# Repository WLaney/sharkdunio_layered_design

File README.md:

# sharkduino_layered_desgine

This repository contains the Eagle designs and design information for the Sharkduino PCBs. The name sharkduino_layered_desgin is a legacy name referring to the design type used by Sharkduino V1. This repository does however contains all versions of Shakrduino, not just V1. Please see [Sharkduino Versions](#sharkduino-versions) for more information. For the spefic chips and ports on each version please see [Hardware Quick Reference](https://github.com/WLaney/sharkdunio_layered_design/blob/master/hardware_quick_reference.md)

# Sharkduino Versions

This is an explanation of the different sharkduino versions and the directories in this repository that contain them

## Sharkduino V1

Sharkduino V1 uses a layer designs and consists of [layer1](layer1/), [layer2](layer2/), and [layer3](layer3/). The versions of Sharkduino V1 that were assembled corresponded to the release v2 named "Layered boards". Changes have been made to the boards since then in order to improve them, these changes constitute Sharkduino V1.1. No V1.1 boards were ever ordered or assembled. Instead of ordering V1.1 boards a design overhaul took place and we moved to Sharkduino V2. 

## Sharkduino V2

Sharkduino V2 constitutes a design overhaul from V1 with a new board shape and new set of sensors. These designs can be found in the [trapezoid](trapezoid/) directory. The version of Sharkduino V2 that has been assembled corresponds to release [v5](https://github.com/WLaney/sharkdunio_layered_design/releases/tag/v5) "Sharkduion V2". Since the enviromental sensors need to be sepreate from the movement sensors Shakrduino V2 still uses [layer3](layer3/) form the Sharkduino V1 as no changes to that board were nessary.

## Sharkduino V2.1

Sharkduino V2.1 is an identical PCB to V2, but it uses the MMA8451 accelerometer. This is opposed to the MMA8452 used in the V2. This change was made so that the accelerometer would have a FIFO bufer like the gyroscope. The new accelerometer is an expermental change, so the files are on the [MMA8451 branch](https://github.com/WLaney/sharkdunio_layered_design/tree/mma8451). The first functinoal build of this corosponds to release [v7](https://github.com/WLaney/sharkdunio_layered_design/releases/tag/v7). The change on this branch have since been merged into master.

## Sharkduino V2.2

Sharkduino V2.2 is a slight varation on the Sharkduino V2.x desgine. Due to the [issue with the cargining circuity](https://github.com/WLaney/sharkdunio_layered_design/issues/1) the microUSB and lipo charger were removed from the board. This was done in order to have a set of fully functional board ready for summer 2017. 

The LiPo plug was moved to the top of the board in order to streamline the desgine. Additionaly interupt pin2 on the FXAS21002 gyroscope was connected Arduino pin 2. 

Since in the long term we plan to fix the LiPo charging issue, instead of removing the LiPo chargin all together as we have done here, the files for Sharkduino V2.2 are on the [no_chargin branch](https://github.com/WLaney/sharkdunio_layered_design/tree/no_charging) and will never be merged into master. The desgines of the Sharkduino V2.2 that have been order corosponed to release [v8](https://github.com/WLaney/sharkdunio_layered_design/releases/tag/v8).

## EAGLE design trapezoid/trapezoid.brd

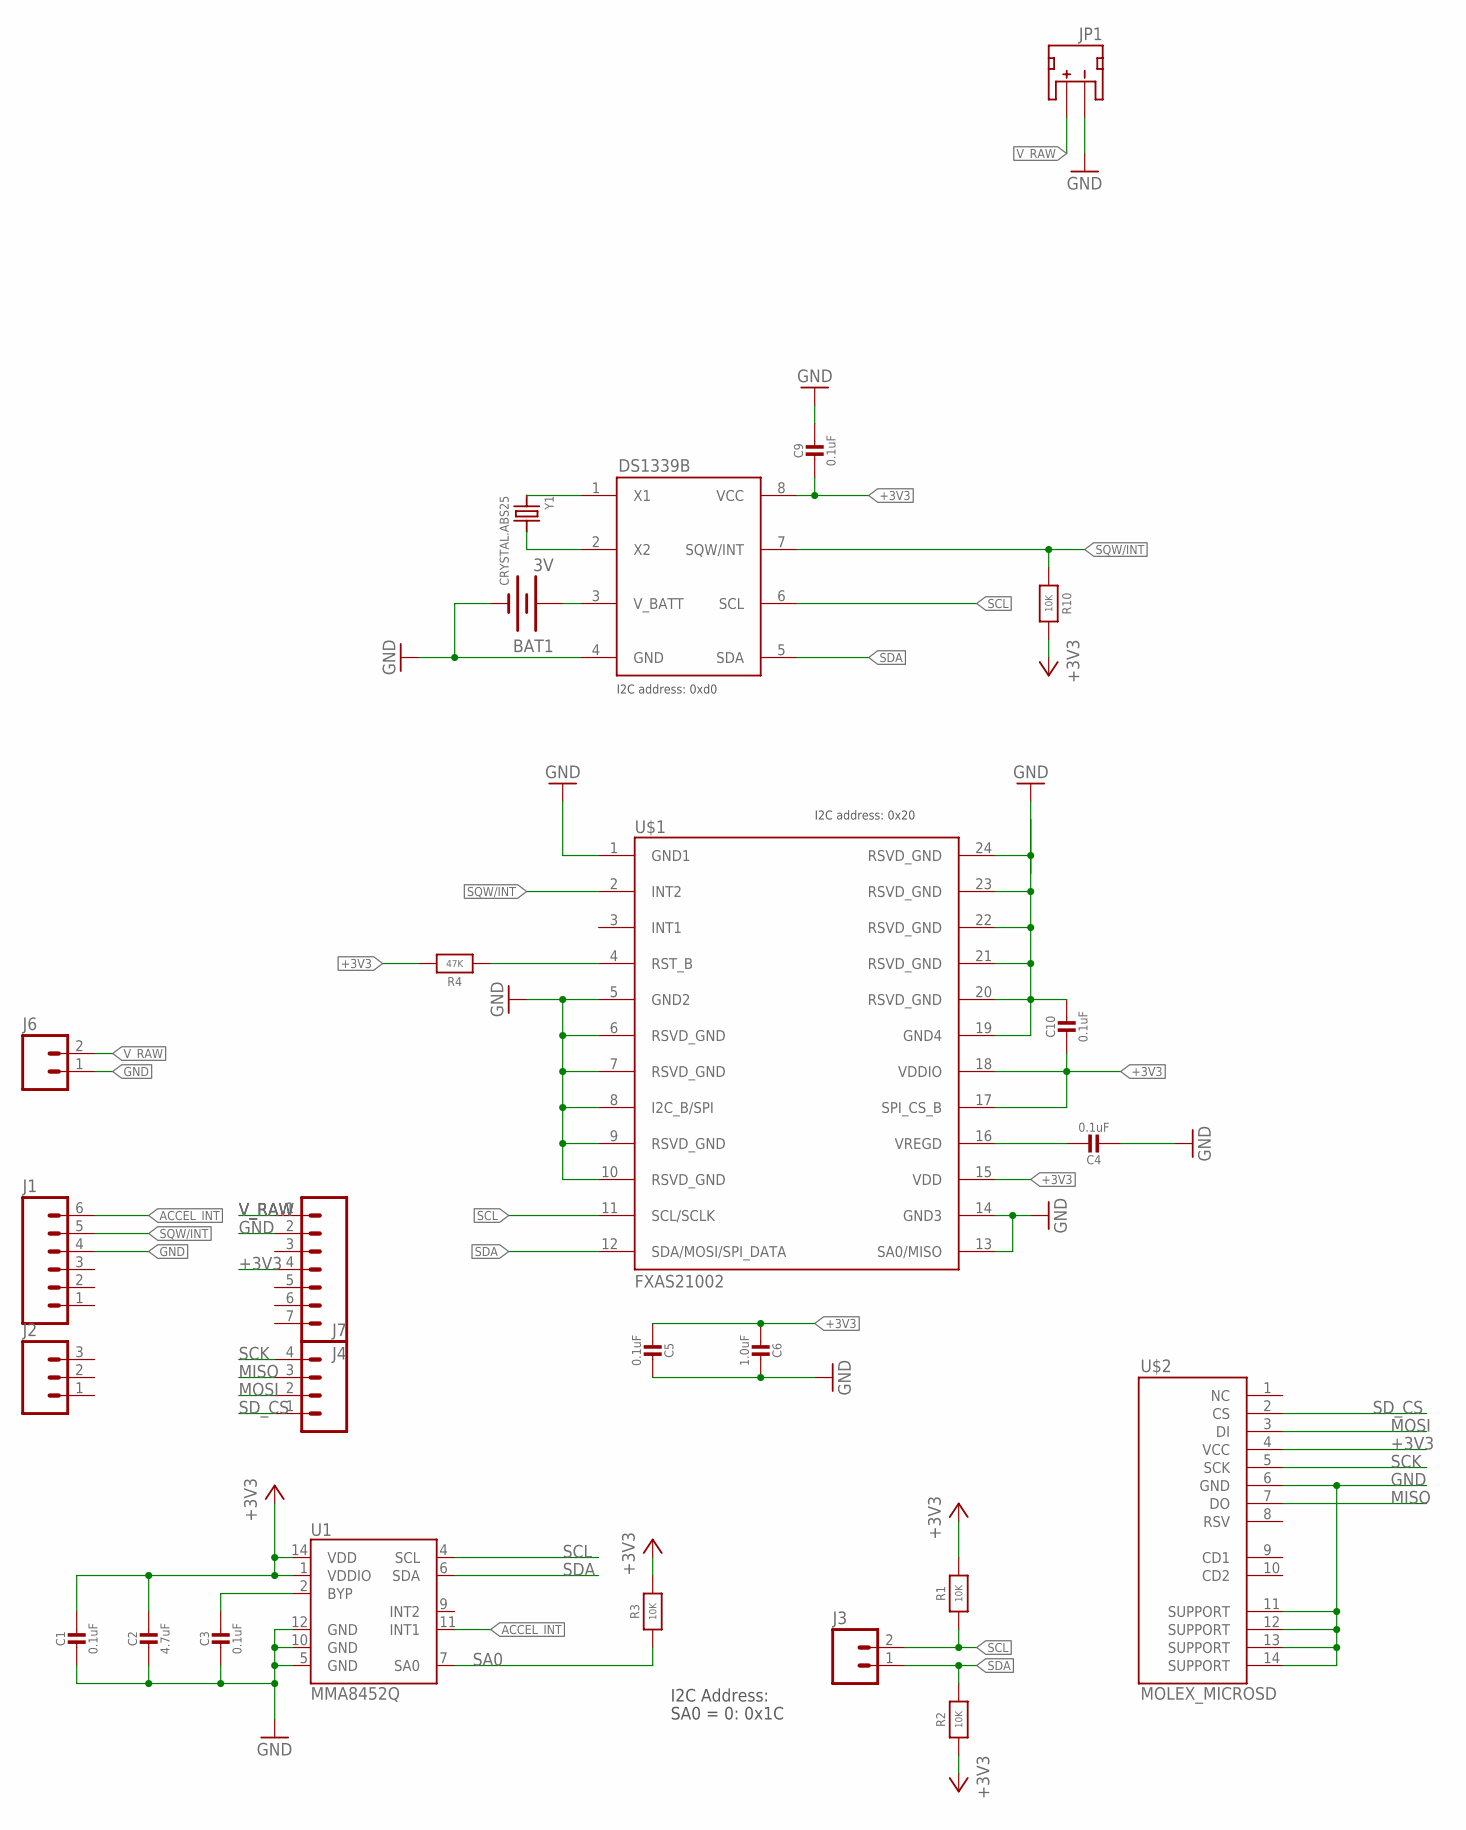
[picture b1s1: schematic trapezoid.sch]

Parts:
BAT1: 3V; BATTCON_12MM_CURVED
C1, C3, C4, C5, C9, C10: 0.1uF; 0805-NO
C2: 4.7uF; 0805-NO
C6: 1.0uF; 0805-NO
J1: M06SILK_FEMALE_PTH; 1X06
J2: M03PTH; 1X03
J3, J6: M02LOCK; 1X02_LOCK
J4: M07; 1X07
J7: M04PTH; 1X04
JP1: JST; JST-2-SMD@1
R1, R2, R10: 10K; 0805-NO
R3: 10K; _0805MP
R4: 47K; 0805-NO
U1: MMA8452Q; QFN-16_0.5MM
U$1: FXAS21002; 24QFN
U$2: MOLEX_MICROSD
U$3: DS1339BDS1339B; 8U-SOP
Y1: CRYSTAL.ABS25; ABS25

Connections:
+3V3: C1.1, C2.1, C5.2, C6.2, C9.2, C10.2, J4.4, R1.2, R2.1, R3.2, R4.2, R10.2, U1.1 (VDDIO), U1.14 (VDD), U$1.15 (VDD), U$1.17 (SPI_CS_B), U$1.18 (VDDIO), U$2.4 (VCC), U$3.8 (VCC)
ACCEL_INT: J1.6, U1.11 (INT1)
BYP: C3.1, U1.2 (BYP)
GND: BAT1.GND (-), C1.2, C2.2, C3.2, C4.2, C5.1, C6.1, C9.1, C10.1, J1.4, J4.2, J6.1, JP1.1 (-), U1.5 (GND), U1.10 (GND), U1.12 (GND), U$1.1 (GND1), U$1.5 (GND2), U$1.6 (RSVD_GND), U$1.7 (RSVD_GND), U$1.8 (I2C_B/SPI), U$1.9 (RSVD_GND), U$1.10 (RSVD_GND), U$1.13 (SA0/MISO), U$1.14 (GND3), U$1.19 (GND4), U$1.20 (RSVD_GND), U$1.21 (RSVD_GND), U$1.22 (RSVD_GND), U$1.23 (RSVD_GND), U$1.24 (RSVD_GND), U$2.6 (GND), U$2.11 (SUPPORT), U$2.12 (SUPPORT), U$2.13 (SUPPORT), U$2.14 (SUPPORT), U$3.4 (GND)
MISO: J7.3, U$2.7 (DO)
MOSI: J7.2, U$2.3 (DI)
unnamed: U$3.2 (X2), Y1.4 (2)
unnamed: C4.1, U$1.16 (VREGD)
unnamed: BAT1.PWR@1 (+), U$3.3 (V_BATT)
unnamed: U$3.1 (X1), Y1.1
unnamed: R4.1, U$1.4 (RST_B)
SA0: R3.1, U1.7 (SA0)
SCK: J7.4, U$2.5 (SCK)
SCL: J3.2, R1.1, U1.4 (SCL), U$1.11 (SCL/SCLK), U$3.6 (SCL)
SDA: J3.1, R2.2, U1.6 (SDA), U$1.12 (SDA/MOSI/SPI_DATA), U$3.5 (SDA)
SD_CS: J7.1, U$2.2 (CS)
SQW/INT: J1.5, R10.1, U$1.2 (INT2), U$3.7 (SQW/INT)
V_RAW: J4.1, J6.2, JP1.2 (+)

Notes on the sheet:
I2C Address:
SA0 = 0: 0x1C
I2C address: 0xd0
I2C address: 0x20

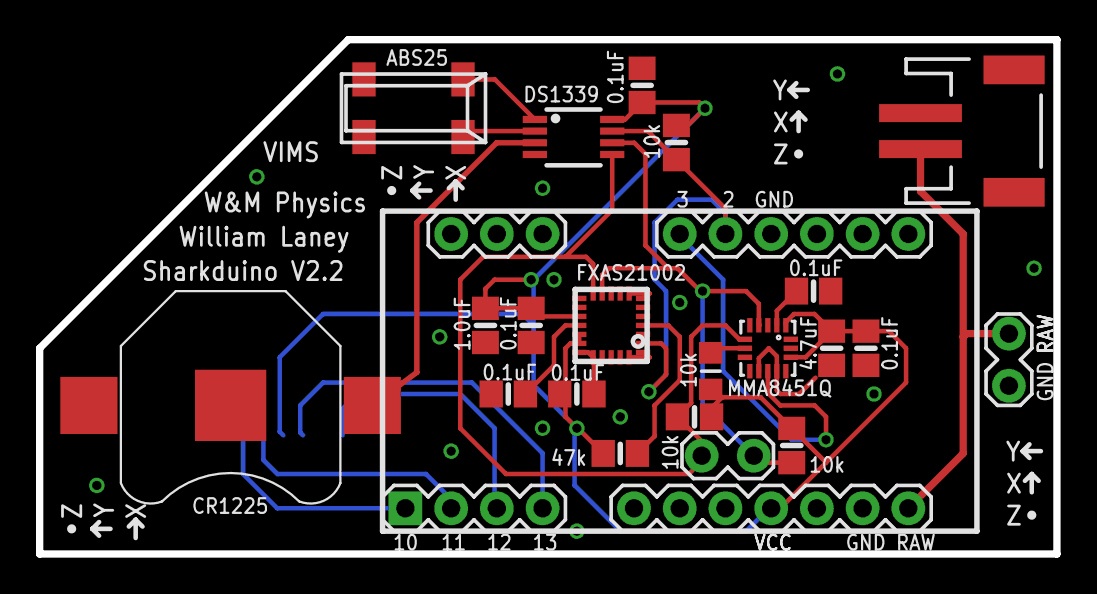
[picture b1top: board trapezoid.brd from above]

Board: 2 copper layers, 56.5 x 28.6 mm, 26 parts (1 on the bottom side), 18 nets.

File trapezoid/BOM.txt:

component/value, size, quanity, digikey part number
--------------------------------------------------------
Arduino Pro Mini 3.3V/8MHz, NA, 1, 1568-1054-ND
MMA8451QT, 16-VFQFN, 1, MMA8451QT-ND
FXAS21002 IC, 24-TFQFN, 1, FXAS21002CQR1CT-ND
DS1339B IC, 8-TSSOP/8-MSOP, 1, DS1339BU+-ND
Abracon LLC ABS25-32.768KHZ-T, 4-SOJ, 1, 535-9166-1-ND
Molex 8+2 microSD slot, NA, 1, WM6357CT-ND
0.1uF capacitor, 0805, 6, 478-3755-1-ND
1.0uF capacitor, 0805, 1, 311-1365-1-ND
4.7uF capacitor, 0805, 1, 490-3335-1-ND
10K resistor, 0805, 4, 311-10.0KCRCT-ND
47k resistor, 0805, 1, 311-47KARCT-ND
Curved Battery Holder, 12mm, 1, 36-3000CT-ND
JST Male, 2mm, 1, 455-1749-1-ND
Male Header Pins, 0.10", 1, S1011EC-40-ND

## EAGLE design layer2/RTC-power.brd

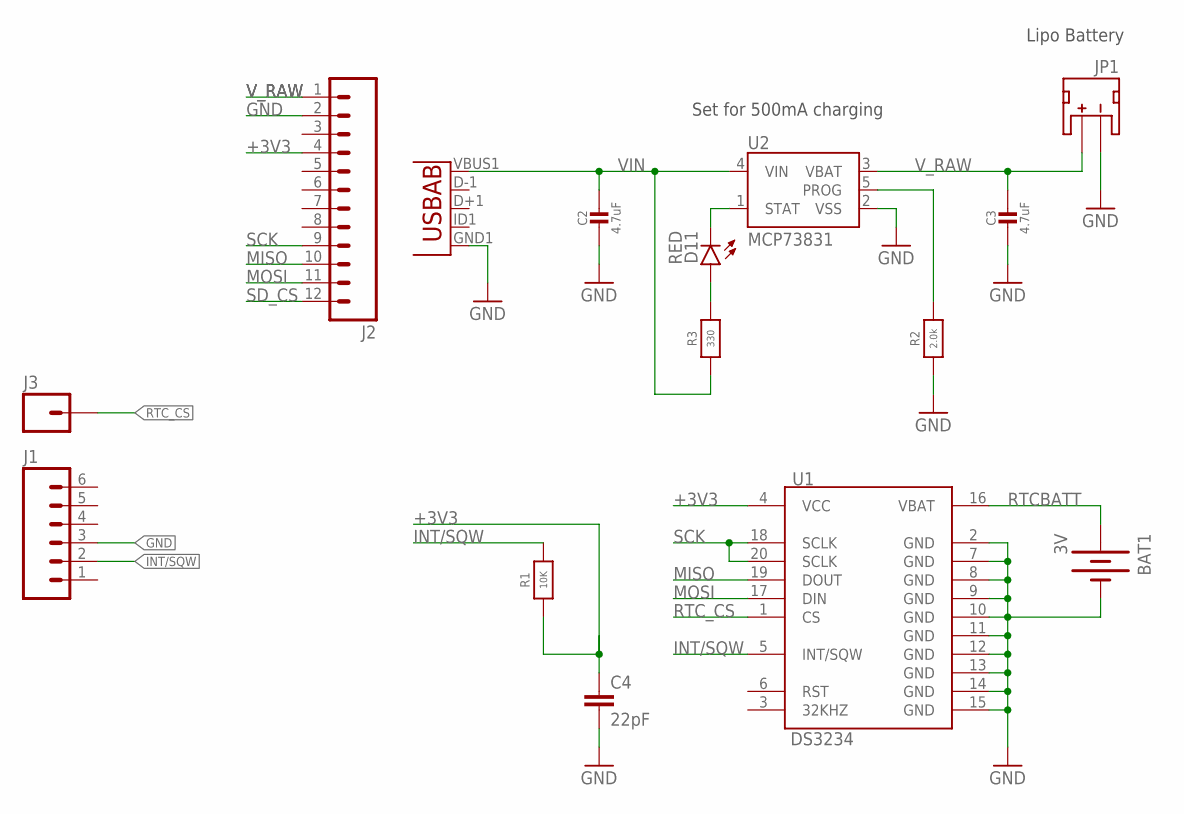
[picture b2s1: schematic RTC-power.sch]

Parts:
BAT1: 3V; BATTCON_12MM_CURVED
C2, C3: 4.7uF; 0805-NO
C4: 22pF; 0402-CAP
D11: RED; LED-0603
J1: M06SILK_FEMALE_PTH; 1X06
J2: M12PTH; 1X12
J3: M01PTH; 1X01
JP1: JST; JST-2-SMD@1
JP9: Micro USB; USB-AB-MICRO-SMD_V03
R1: 10K; _0805MP
R2: 2.0k; _0805MP
R3: 330; _0805MP
U1: DS3234
U2: MCP73831; SOT23-5

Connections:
+3V3: C4.1, J2.4, R1.1, U1.4 (VCC)
GND: BAT1.GND (-), C2.2, C3.2, C4.2, J2.2, JP1.1 (-), JP9.GND1 (GND), R2.1, U1.2 (GND), U1.7 (GND), U1.8 (GND), U1.9 (GND), U1.10 (GND), U1.11 (GND), U1.12 (GND), U1.13 (GND), U1.14 (GND), U1.15 (GND), U2.2 (VSS)
INT/SQW: R1.2, U1.5 (INT/SQW)
MISO: J2.10, U1.19 (DOUT)
MOSI: J2.11, U1.17 (DIN)
unnamed: D11.A, R3.2
PROG: R2.2, U2.5 (PROG)
RTCBATT: BAT1.PWR@1 (+), U1.16 (VBAT)
RTC_CS: J3.1, U1.1 (CS)
SCK: J2.9, U1.18 (SCLK), U1.20 (SCLK)
SD_CS: J2.12
STAT: D11.C, U2.1 (STAT)
VIN: C2.1, JP9.VBUS1 (VBUS), R3.1, U2.4 (VIN)
V_RAW: C3.1, J2.1, JP1.2 (+), U2.3 (VBAT)

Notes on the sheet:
Set for 500mA charging
Lipo Battery

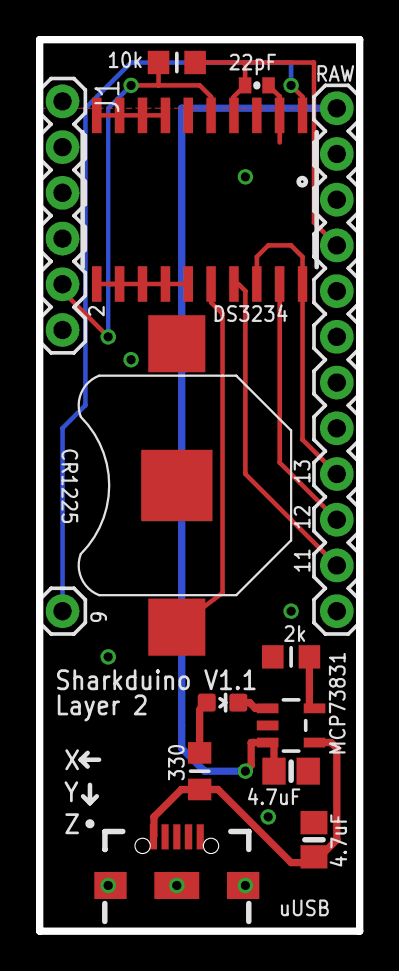
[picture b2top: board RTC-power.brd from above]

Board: 2 copper layers, 17.8 x 49.5 mm, 15 parts (1 on the bottom side), 13 nets.

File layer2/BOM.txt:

component/value, size, quanity, digikey part number
--------------------------------------------------------
4.7uF capacitor, 0805, 2, 490-3335-1-ND
22pF capacitor, 0402, 1, 399-7774-1-ND
Red LED, 0603, 1, 160-1447-1-ND
10K resistor, 0805, 1, 311-10.0KCRCT-ND
2k resistor, 0805, 1, 311-2.00KCRCT-ND
330 resistor, 0805, 1, 311-330CRCT-ND
DS3234 IC, NA, 1, 	DS3234S#T&RCT-ND
MCP73831 IC, NA, 1, MCP73831T-2ATI/OTCT-ND
Curved Battery Holder, 12mm, 1, 36-3000CT-ND
JST Male, 2mm, 1, 455-1704-ND *NOT THE RIGHT PART*
USB micro SMD, NA, 1, 609-4053-1-ND
Header Pins, NA, 1, S1131EC-40-ND

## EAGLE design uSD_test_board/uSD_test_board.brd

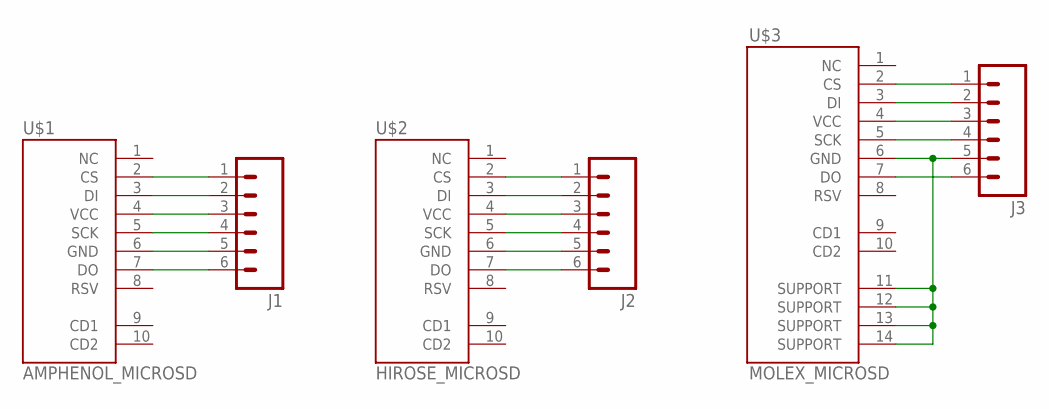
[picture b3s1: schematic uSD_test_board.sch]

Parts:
J1, J2, J3: M06SILK_FEMALE_PTH; 1X06
U$1: AMPHENOL_MICROSD
U$2: HIROSE_MICROSD; AMPHENOL_MICROSD
U$3: MOLEX_MICROSD

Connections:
CS1: J1.1, U$1.2 (CS)
CS2: J2.1, U$2.2 (CS)
CS3: J3.1, U$3.2 (CS)
DI1: J1.2, U$1.3 (DI)
DI2: J2.2, U$2.3 (DI)
DI3: J3.2, U$3.3 (DI)
DO1: J1.6, U$1.7 (DO)
DO2: J2.6, U$2.7 (DO)
DO3: J3.6, U$3.7 (DO)
GND: J1.5, J2.5, J3.5, U$1.6 (GND), U$2.6 (GND), U$3.6 (GND), U$3.11 (SUPPORT), U$3.12 (SUPPORT), U$3.13 (SUPPORT), U$3.14 (SUPPORT)
SCK1: J1.4, U$1.5 (SCK)
SCK2: J2.4, U$2.5 (SCK)
SCK3: J3.4, U$3.5 (SCK)
VCC1: J1.3, U$1.4 (VCC)
VCC2: J2.3, U$2.4 (VCC)
VCC3: J3.3, U$3.4 (VCC)

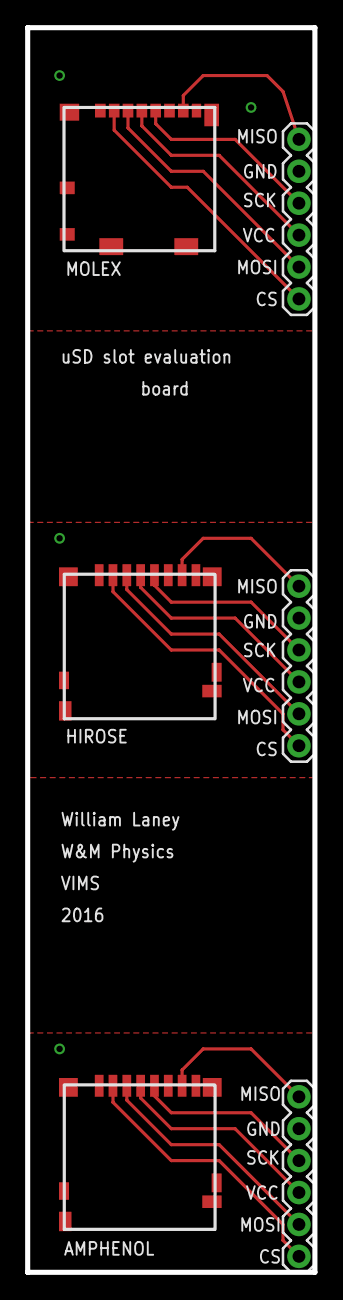
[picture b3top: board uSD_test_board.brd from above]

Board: 2 copper layers, 22.9 x 99.1 mm, 6 parts (0 on the bottom side), 16 nets.

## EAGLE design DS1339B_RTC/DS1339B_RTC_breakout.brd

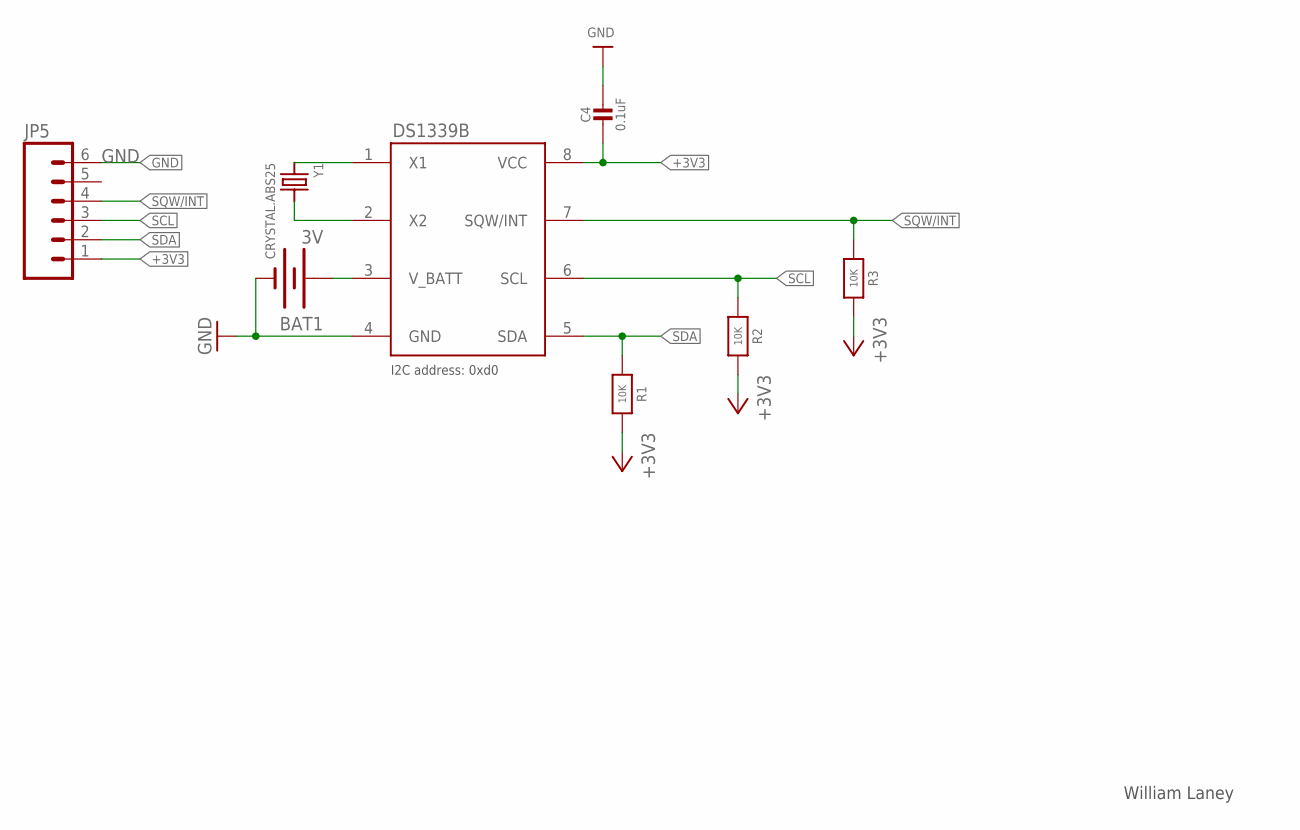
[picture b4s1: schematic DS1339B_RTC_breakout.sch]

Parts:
BAT1: 3V; BATTCON_12MM_CURVED
C4: 0.1uF; 0805-NO
JP5: M06SIP; 1X06
R1, R2, R3: 10K; 0805-NO
U$1: DS1339BDS1339B; 8U-SOP
Y1: CRYSTAL.ABS25; ABS25

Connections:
+3V3: C4.2, JP5.1, R1.2, R2.2, R3.2, U$1.8 (VCC)
GND: BAT1.GND (-), C4.1, JP5.6, U$1.4 (GND)
unnamed: U$1.1 (X1), Y1.1
unnamed: U$1.2 (X2), Y1.4 (2)
unnamed: BAT1.PWR@1 (+), U$1.3 (V_BATT)
SCL: JP5.3, R2.1, U$1.6 (SCL)
SDA: JP5.2, R1.1, U$1.5 (SDA)
SQW/INT: JP5.4, R3.1, U$1.7 (SQW/INT)

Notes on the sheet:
I2C address: 0xd0
William Laney

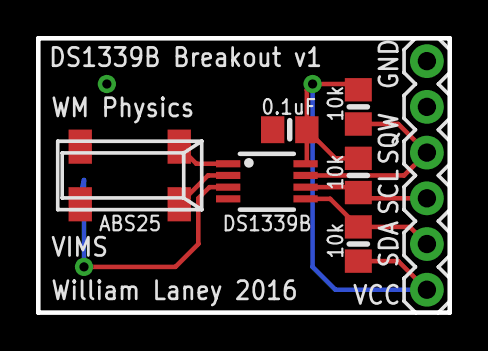
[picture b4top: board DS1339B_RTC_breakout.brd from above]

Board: 2 copper layers, 22.9 x 15.2 mm, 8 parts (1 on the bottom side), 8 nets.

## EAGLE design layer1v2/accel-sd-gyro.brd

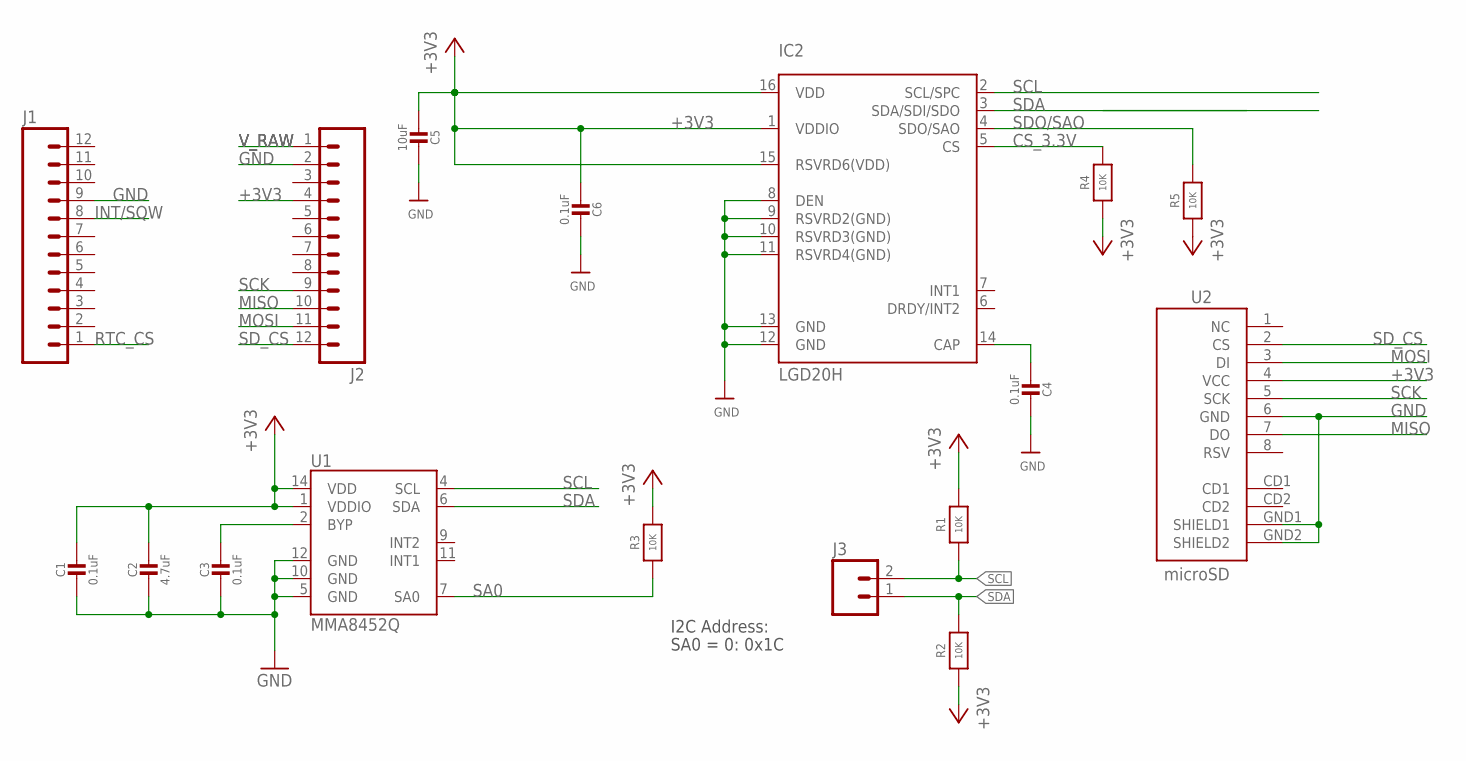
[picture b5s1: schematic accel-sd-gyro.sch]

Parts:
C1, C3, C4, C6: 0.1uF; 0805-NO
C2: 4.7uF; 0805-NO
C5: 10uF; 0805-NO
IC2: LGD20H; L3GD20H_LGA16L
J1, J2: M12PTH; 1X12
J3: M02LOCK; 1X02_LOCK
R1, R2, R4, R5: 10K; 0805-NO
R3: 10K; _0805MP
U1: MMA8452Q; QFN-16_0.5MM
U2: microSD; MICRO-SD-SOCKET-PP

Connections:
+3V3: C1.1, C2.1, C5.2, C6.2, IC2.1 (VDDIO), IC2.15 (RSVRD6(VDD)), IC2.16 (VDD), J2.4, R1.2, R2.1, R3.2, R4.1, R5.1, U1.1 (VDDIO), U1.14 (VDD), U2.4 (VCC)
BYP: C3.1, U1.2 (BYP)
CS_3.3V: IC2.5 (CS), R4.2
GND: C1.2, C2.2, C3.2, C4.1, C5.1, C6.1, IC2.8 (DEN), IC2.9 (RSVRD2(GND)), IC2.10 (RSVRD3(GND)), IC2.11 (RSVRD4(GND)), IC2.12 (GND), IC2.13 (GND), J1.9, J2.2, U1.5 (GND), U1.10 (GND), U1.12 (GND), U2.6 (GND), U2.GND1 (SHIELD1), U2.GND2 (SHIELD2)
INT/SQW: J1.8
MISO: J2.10, U2.7 (DO)
MOSI: J2.11, U2.3 (DI)
unnamed: C4.2, IC2.14 (CAP)
RTC_CS: J1.1
SA0: R3.1, U1.7 (SA0)
SCK: J2.9, U2.5 (SCK)
SCL: IC2.2 (SCL/SPC), J3.2, R1.1, U1.4 (SCL)
SDA: IC2.3 (SDA/SDI/SDO), J3.1, R2.2, U1.6 (SDA)
SDO/SAO: IC2.4 (SDO/SAO), R5.2
SD_CS: J2.12, U2.2 (CS)
V_RAW: J2.1

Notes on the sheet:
I2C Address:
SA0 = 0: 0x1C

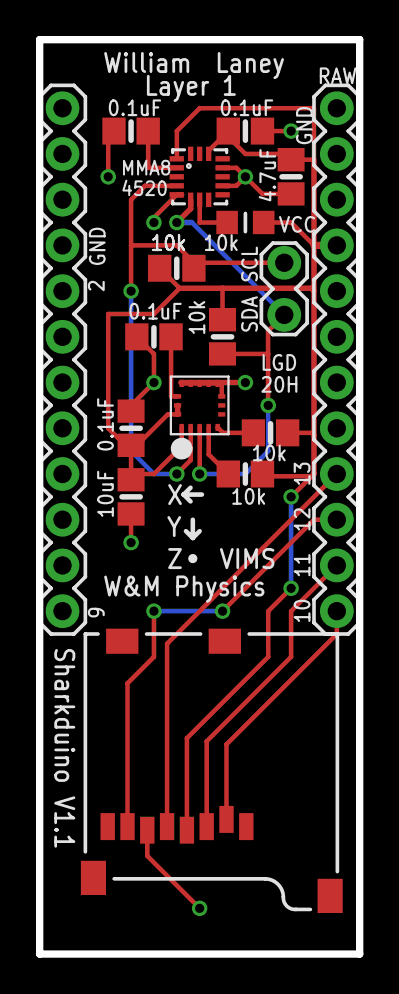
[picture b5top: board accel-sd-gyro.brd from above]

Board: 2 copper layers, 17.8 x 50.8 mm, 17 parts (0 on the bottom side), 13 nets.

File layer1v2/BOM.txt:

component/value, size, quanity, digikey part number
--------------------------------------------------------
0.1uF capacitor, 0805, 4, 478-3755-1-ND
4.7uF capacitor, 0805, 1, 490-3335-1-ND
10uF capacitor, 0805, 1, 490-4735-1-ND
10K resistor, 0805, 4, 311-10.0KCRCT-ND
MMA8452QT, NA, 1, 	MMA8452QT-ND
L3GD20HTR IC, NA, 1, 497-13931-1-ND
microSD SMD, NA, 1, Sparkfun: PRT-00127

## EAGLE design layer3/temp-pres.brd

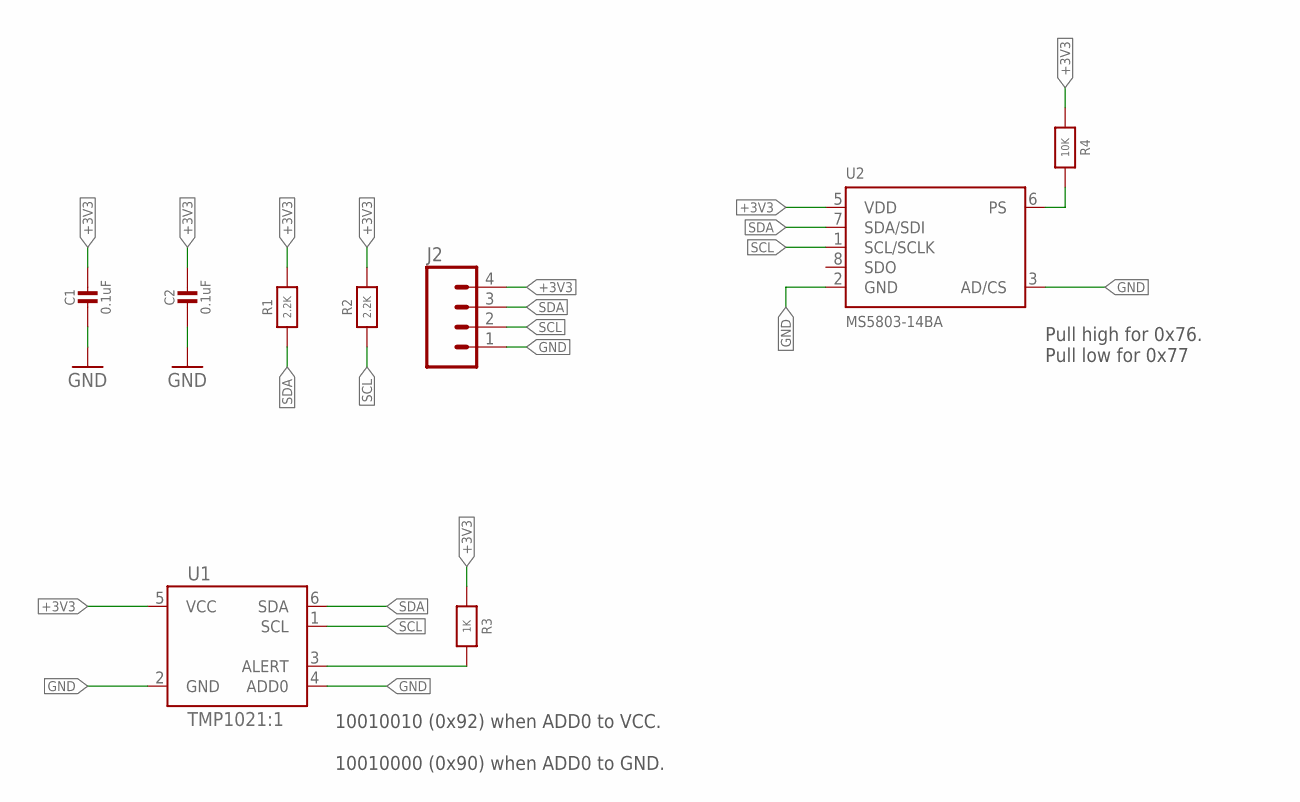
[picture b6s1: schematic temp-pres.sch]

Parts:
C1, C2: 0.1uF; 0805-NO
J2: M04NO_SILK_ALL_ROUND; 1X04_NO_SILK_ALL_ROUND
R1, R2: 2.2K; _0805MP
R3: 1K; _0805MP
R4: 10K; _0805MP
U1: TMP1021:1; SOT563-2
U2: MS5803-14BA; MS5803

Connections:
+3V3: C1.1, C2.1, J2.4, R1.2, R2.2, R3.1, R4.1, U1.5 (VCC), U2.5 (VDD)
GND: C1.2, C2.2, J2.1, U1.2 (GND), U1.4 (ADD0), U2.2 (GND), U2.3 (AD/CS)
unnamed: R3.2, U1.3 (ALERT)
PS: R4.2, U2.6 (PS)
SCL: J2.2, R2.1, U1.1 (SCL), U2.1 (SCL/SCLK)
SDA: J2.3, R1.1, U1.6 (SDA), U2.7 (SDA/SDI)

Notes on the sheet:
10010010 (0x92) when ADD0 to VCC. 10010000 (0x90) when ADD0 to GND.
Pull high for 0x76. Pull low for 0x77

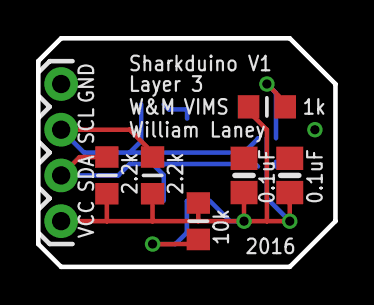
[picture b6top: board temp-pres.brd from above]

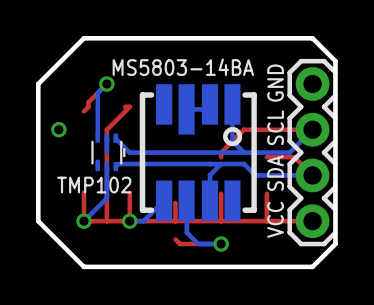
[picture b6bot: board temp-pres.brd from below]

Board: 2 copper layers, 16.5 x 12.7 mm, 9 parts (2 on the bottom side), 6 nets.

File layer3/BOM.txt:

component/value, size, quanity, digikey part number
--------------------------------------------------------
10K resistor, 0805, 1, 311-10.0KCRCT-ND
2.2K resistor, 0805, 2, 311-2.20KCRCT-ND
1k resostor, 0805, 1, 311-1.00KCRCT-ND
0.1uF capacitor, 0805, 2, 478-3755-1-ND
TMP102 IC, NA, 1, 296-26834-1-ND
MS5803-14BA IC, NA, 1, 223-1626-5-ND

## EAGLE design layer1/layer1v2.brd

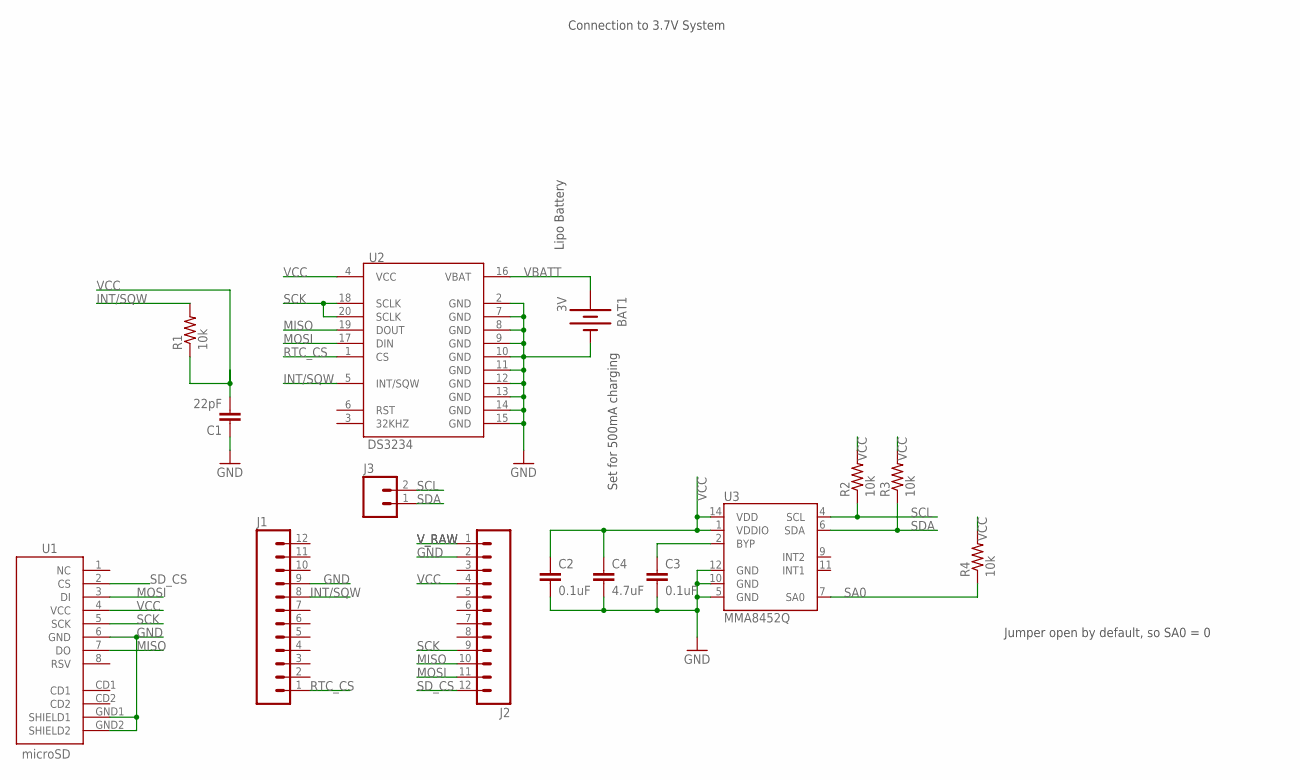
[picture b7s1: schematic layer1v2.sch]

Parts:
BAT1: 3V; BATTCON_12MM_CURVED
C1: 22pF; 0402-CAP
C2, C3: 0.1uF; 0402-CAP
C4: 4.7uF; 0402-CAP
J1, J2: M12PTH; 1X12
J3: M02LOCK; 1X02_LOCK
R1, R2, R3, R4: 10k; 0402-RES
U1: microSD; MICRO-SD-SOCKET-PP
U2: DS3234
U3: MMA8452Q; QFN-16_0.5MM

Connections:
BYP: C3.1, U3.2 (BYP)
GND: BAT1.GND (-), C1.1, C2.2, C3.2, C4.2, J1.9, J2.2, U1.6 (GND), U1.GND1 (SHIELD1), U1.GND2 (SHIELD2), U2.2 (GND), U2.7 (GND), U2.8 (GND), U2.9 (GND), U2.10 (GND), U2.11 (GND), U2.12 (GND), U2.13 (GND), U2.14 (GND), U2.15 (GND), U3.5 (GND), U3.10 (GND), U3.12 (GND)
INT/SQW: J1.8, R1.2, U2.5 (INT/SQW)
MISO: J2.10, U1.7 (DO), U2.19 (DOUT)
MOSI: J2.11, U1.3 (DI), U2.17 (DIN)
RTC_CS: J1.1, U2.1 (CS)
SA0: R4.1, U3.7 (SA0)
SCK: J2.9, U1.5 (SCK), U2.18 (SCLK), U2.20 (SCLK)
SCL: J3.2, R2.1, U3.4 (SCL)
SDA: J3.1, R3.1, U3.6 (SDA)
SD_CS: J2.12, U1.2 (CS)
VBATT: BAT1.PWR@1 (+), U2.16 (VBAT)
VCC: C1.2, C2.1, C4.1, J2.4, R1.1, R2.2, R3.2, R4.2, U1.4 (VCC), U2.4 (VCC), U3.1 (VDDIO), U3.14 (VDD)
V_RAW: J2.1

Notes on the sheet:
Set for 500mA charging
Connection to 3.7V System
Lipo Battery
Jumper open by default, so SA0 = 0

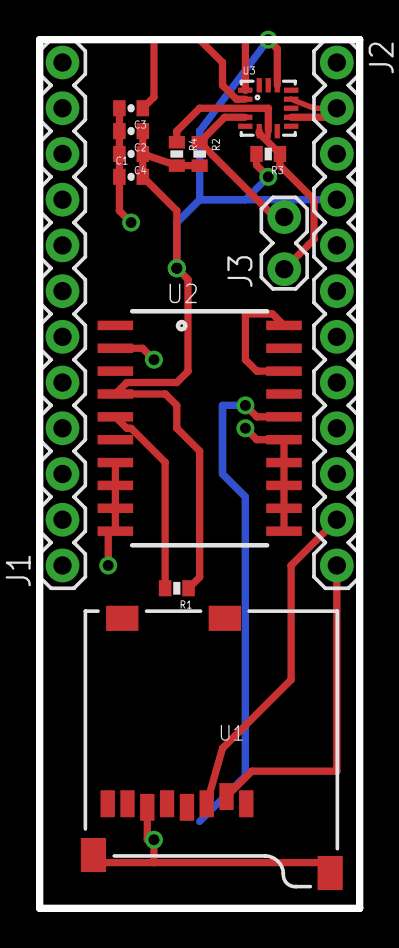
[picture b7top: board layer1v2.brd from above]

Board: 2 copper layers, 17.8 x 48.3 mm, 15 parts (1 on the bottom side), 13 nets.

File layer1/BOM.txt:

component/value, size, quanity, digikey part number
--------------------------------------------------------
0.1uF capacitor, 0805, 4, 478-3755-1-ND
4.7uF capacitor, 0805, 1, 490-3335-1-ND
10uF capacitor, 0805, 1, 490-4735-1-ND
10K resistor, 0805, 4, 311-10.0KCRCT-ND
MMA8452QT, 16-VFQFN, 1, 	MMA8452QT-ND
L3GD20HTR IC, 16-LGA, 1, 497-13931-1-ND
microSD SMD, NA, 1, Sparkfun: PRT-00127

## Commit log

2016-06-10 creaded design file
2016-06-10 added batteri connection to board
2016-06-10 I don't know why eagles file thing hates me, but here we are
2016-06-10 removed battery, add accel
2016-06-13 who needs commits
2016-06-14 layer 1 with diff componets
2016-06-14 added gyro
2016-06-14 added sd
2016-06-14 added headers
2016-06-14 finishing touches on schematic
2016-06-14 creaded layout
2016-06-15 created layout for just the gyro
2016-06-15 boards rounted with silk screen
2016-06-15 shortedn connections, removed via
2016-06-15 rottated header 180 degrees
2016-06-15 added six pin header to stack with accell
2016-06-15 set up pins to line up with accel corectly
2016-06-15 minor placment adjustments
2016-06-16 final touches
2016-06-16 final verson to submit to osh park for protyping
2016-06-16 adjusted tname and tvalue layers
2016-06-17 adjusted silk screen layout
2016-06-23 intial layout of v2 board, consldated i2c resisor, added header pin row
2016-06-24 layer 1 tweaks and silk
2016-06-27 begun layer 2 desgine
2016-06-27 Initail board argment
2016-06-27 real intial board layout
2016-06-28 layed out all conectons on board
2016-06-28 replaced ground wires with top layer ground plane
2016-06-28 removed unneeded header to give battery access
2016-06-28 silk screen adjustment
2016-06-28 silk screen
2016-06-30 added bom
2016-06-30 increased charging wire width
2016-06-30 added bottom silk screen
2016-07-05 removed via under sd
2016-07-05 tweaked silk screen and spread out some componets slightly
2016-07-06 added bill of materials
2016-07-06 slight tweaks
2016-07-07 tweacked sd traces
2016-07-07 created BOM
2016-07-07 final chnages before ordering
2016-07-08 created pressure sensor temp sensor sychmatic
2016-07-08 intital board layout
2016-07-08 added documintation
2016-07-08 who knows, probably just opened the file
2016-07-08 diangonalized coners to make smaller
2016-07-08 removed serial data output (SDO) from schematic bc it is not needed. Since it is an output I blieve it is safe to let it float.
2016-07-08 added silk screen
2016-07-11 added documentation of board
2016-07-11 removed residual layer1 directory
2016-07-11 documentation
2016-07-11 tweeaked resistor placement
2016-07-12 added clearnece between components and leads
2016-07-12 calrified commints
2016-07-12 created bill of materals
2016-07-12 updated bom
2016-07-12 created documentation
2016-07-12 updated documentation with contact info
2016-07-12 feture request for future versions
2016-07-13 tweaked layer3 silk screen for printing
2016-07-13 updated BOM to reflect digikey shipment
2016-07-15 updated documentation
2016-07-15 Proofread gyroscope/documentation.txt
    Grammar, spelling updates. Clarified nature of axis/rotation labels.
2016-07-15 layer 1v2 proofread
    Grammar, spelling, clarity updates
2016-07-15 Proofread layer2.txt
    Grammar, spelling, clarity
2016-07-15 layer3 proofreading
    Spelling, grammar, clarity
2016-07-15 Update documentation.txt
    update
2016-07-21 updated feture request
2016-07-29 Updated documentation Added assembely instruction, changed formating, and updated feture requests
2016-08-05 slight tweaks to genrate images for poster
2016-08-30 extned layer 1 length to fit uSD
2016-08-30 silk screen changes, added top ground pour, updated doc
2016-08-30 silk screen update
2016-08-30 removed pin 4, movved batt holder
2016-08-30 fixed typo
2016-08-30 add info about soldered protype
    add schematics and assembly instructions
2016-09-05 added prototype documentation
2016-09-16 created trapazoid layout
2016-09-16 postiotedn arduino pins on board
2016-09-16 postiotend arduino pins on board correctly
2016-09-16 possistioned i2c pins
2016-09-17 schematica and intial package for ds1339
2016-09-17 finished ds1339 part
2016-09-17 clean up
2016-09-19 added library from git hub for osscilator
2016-09-19 added lbr read me
2016-09-19 created ds1339b breakout schematic
2016-09-19 added information
2016-09-19 intial layout of breakout board
2016-09-20 created intial board layout
2016-09-20 updated documentation to reflect chargin circuit debugging
2016-09-22 created a bom
2016-09-26 final changes
2016-09-26 chnaged rtc to ds1339b in trap
2016-09-26 rotated pro mini
2016-09-26 placed rtc and usd
2016-09-26 placed accel and gyro
2016-09-27 fully connected schematics
    had to remove some header pin spots to run wire
2016-09-27 decreased board size
2016-09-27 added gnd vias
2016-09-27 shifted everything so pro mini would not over hang board
2016-09-27 moved usb out form under pro mini
2016-09-28 added documentation
2016-09-28 updated doc
2016-09-29 put onto 0.025in grid
2016-09-29 tweaks
2016-09-29 corectly possitoned i2c pins
2016-09-30 compled intial layout and connections
2016-09-30 small optimizations
2016-10-13 centered arduino on board
2016-10-13 put uSD on bottom layer
2016-10-13 shortened board
2016-10-13 changed from 4pin to 3pin header to fit uSD
2016-10-13 roated uUSB and shortened board
2016-10-13 fully routed
2016-10-16 small tweak
2016-10-16 updated doc to include ds1339 assembly instructions
2016-10-18 created new gyro syomble
2016-10-18 created new gyro package
2016-10-20 finished new gyro part
2016-10-20 intial fxas gyro breakout schematic
2016-10-20 chnaged i2c pull up resisotr to 10k
    this may not work, if that is the case its okay, I can just put a 4k7 resitor
    on the board,
2016-10-20 created new gyro board
2016-10-21 all wires connected
2016-10-21 changed int2 pin
    did this to shorten trace to int2
2016-10-21 added silk
2016-10-21 added silk pin 1 dot
2016-10-21 pretty uped silk
2016-10-21 unified units
2016-10-24 created amphenol uSD schematic
2016-10-24 created amphenol layout and device
2016-10-25 changed micro sd symbol name
    this makes it clearer that it is reusable for multiple uSD parts
2016-10-25 new uSD symbol for holder with ground supports
2016-10-25 created molex uSD part
2016-10-25 created molex uSD device
2016-10-27 added hirsch usd
2016-10-27 cread schematic for uSD test board
    board will let me test three final uSD slots in consideration for sharkduino
2016-10-27 named nets
2016-10-27 created uSD test board
2016-10-28 prep for fab
2016-10-31 created uSD test BOM
2016-10-31 uSD test documentation
2016-11-01 created documentation for FXSA gyro
2016-11-01 renamed layer1 directory
2016-11-09 updated uSD part silk
2016-11-12 update doc
2016-11-12 changed gyro in schematic
2016-11-14 fully routed board
2016-11-14 shortend routes
2016-11-14 add raw voltage headers
    allow for easy attachment of inductive charging
2016-11-14 put new uSD slot on board
2016-11-17 silk
2016-11-17 shrunk board
2016-11-17 moved uSD
2016-11-17 grounded uUSB
2016-11-18 preped for buying
2016-11-18 broke out accel int
2016-11-18 final changes before order
2016-11-29 updaed layer 2 BOM JST conector
    changed the JST connector the correct one used in the schematics
2016-11-29 added package sizes to BOM
    IC size was formely NA now it has the package type of the IC
2016-11-29 created sharkduino v2 documentation
2016-12-01 creaded procedues for OSH park order
    added checklist to insure board quality before it sent to be manufactured
2016-12-01 fixed BOM typo
2016-12-01 created a simple BOM convetor
2016-12-01 ignore csv files
    ignore the digikey BOMs generated by the BOM convertor
2016-12-01 fixed readme typo
2016-12-09 added assembly instructions
2017-01-23 unified trace width
2017-01-24 fixed external power headers
    conected external power headers to unrgulated side of rulgulator
    instead of regulated
2017-01-24 solk screen tweak
2017-01-24 updated documentation to reflect changes
2017-01-26 moved DS1339B, FXAS gyro, and L3 gyro to opensoure repos
    these repos can be found at:
    https://github.com/WLaney/DS1339B-RTC-PCB
    https://github.com/WLaney/FXAS21002-gyro-PCB
    https://github.com/WLaney/L3GD20H-gyro-PCB
2017-01-31 trap: small tweak to silk
2017-02-08 added readme file
2017-02-12 updated v2 documentation
    made the assempbly instructions more explicit
2017-02-23 updated trap doc assembly instructions
2017-02-23 updated trap info for new accel
    changed all desgines and info from mma8452 accel to mma8452
2017-02-23 updated readme with v2.1 info
2017-02-24 updated git ignore for csv files
2017-02-24 doc for new accel
2017-03-15 fixed merge artifact in doc
2017-03-15 removed chargin circuity from schematic
    also rerouted battery header pins to connect directly to battery (there is no charger for them to go into any more)
    the board layout has not been updated to reflect this change
2017-03-15 removed all charging circuity from board
    removed all silk, routes, and vias assocated with the chargin circuity and batt
2017-03-15 put JPL on top and routed
2017-03-15 updated readme to reflect merge
2017-03-17 connect gyro int2 to pin3
2017-03-18 increased spacing between gyro and accel by .025in
2017-03-20 removed chargin components from BOM
2017-03-20 final changes for order
    tweaked the silk, and got rid of component names
2017-03-22 small wire rerout to avoid overlap
2017-03-23 updated readme with Sharkduino V2.2 info
2017-03-23 gyro int is on Arduino pin2 not 3
2017-03-23 updated documentation for V2.2
2017-03-24 update doc naming
2017-04-01 added coin cell to BOM
2017-04-07 update documentation
2017-04-14 removed lipo charging info from doc
2017-04-14 created hardware quick refrence
    Looking through individual documentation for each tag is hard, so this is a quick reference of the hardware changes
2017-04-14 added link to hardware quick refrence
2017-10-02 fixed typos
2017-10-02 added second OSH park DRC run
2017-10-09 updated hardware quick ref
2017-10-31 added through hole microUSB part
2017-11-08 added drawings and datasheets
2017-11-16 found I2C addresses
2017-12-12 micro usb part tweeks
    moved pins on schematic to be in same order as on ground pattern

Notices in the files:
parts and their libraries:
SparkFun-Aesthetics: Licensing: Creative Commons ShareAlike 4.0 International - https://creativecommons.org/licenses/by-sa/4.0
SparkFun-Sensors: Licensing: CC v3.0 Share-Alike You are welcome to use this library for commercial purposes.
